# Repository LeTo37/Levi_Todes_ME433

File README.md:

# Levi_Todes_ME433
Advanced Mechatronics Homeworks

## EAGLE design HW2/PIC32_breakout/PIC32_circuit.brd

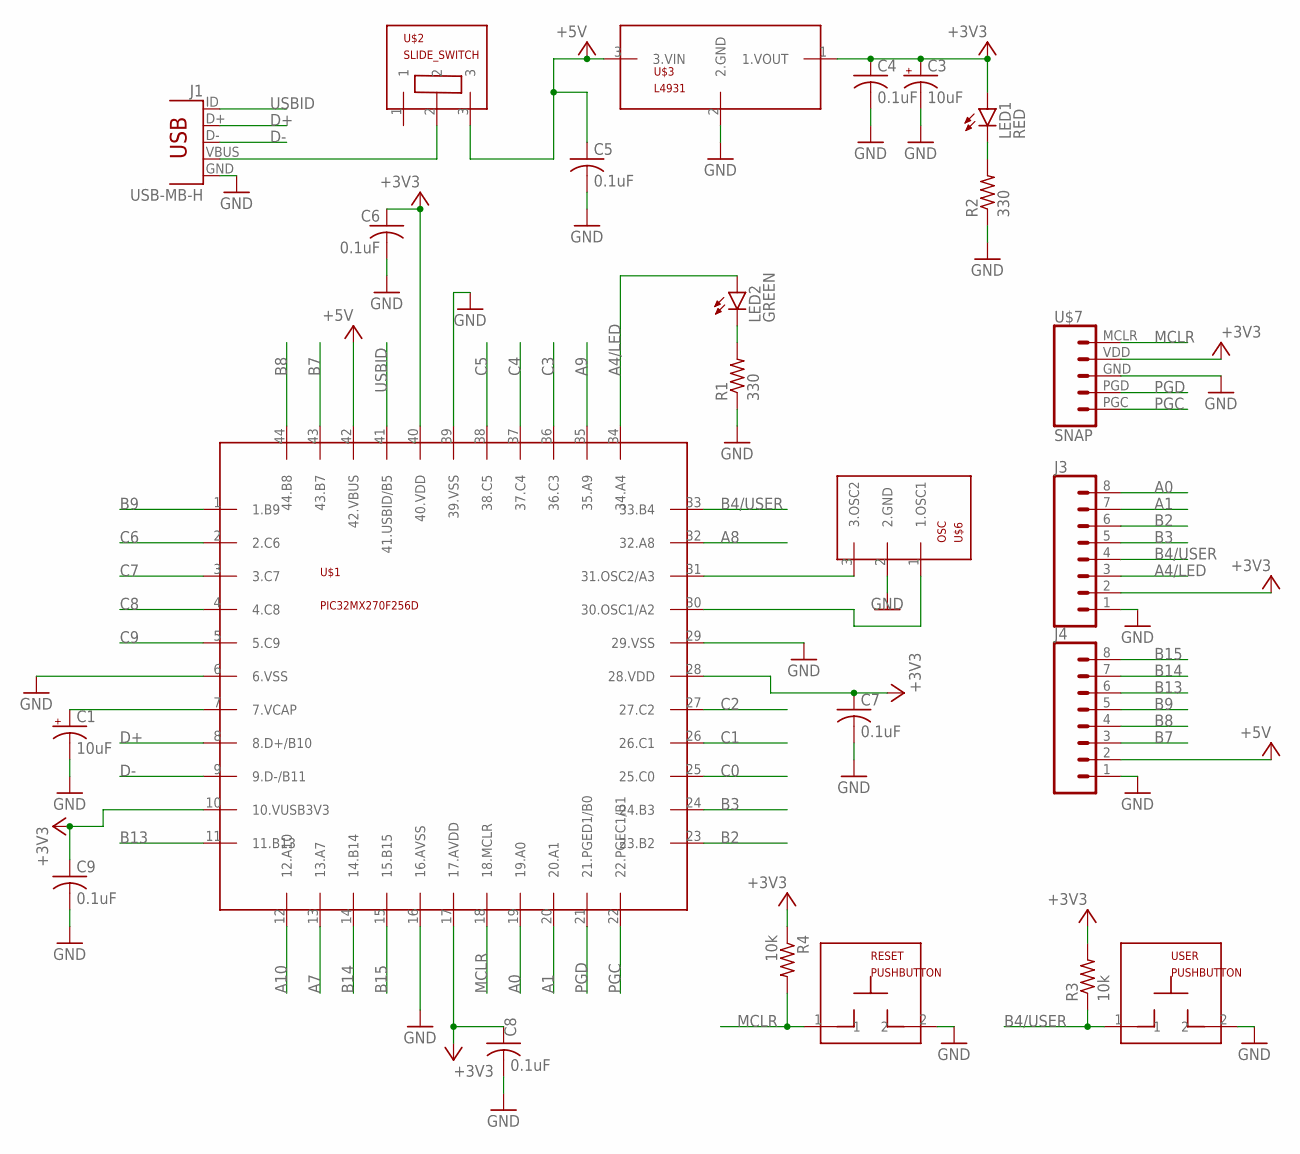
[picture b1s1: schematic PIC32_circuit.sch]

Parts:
C1, C3: 10uF; B45181B
C4, C5, C6, C7, C8, C9: 0.1uF; C025-025X050
J1: USB-MB-H
J3, J4: CONN_08"; 1X08
LED1: RED; LED3MM
LED2: GREEN; LED3MM
R1, R2: 330; 0207/10
R3, R4: 10k; 0207/10
RESET: PUSHBUTTON
U$1: PIC32MX270F256D; TQFP44
U$2: SLIDE_SWITCH
U$3: L4931; TO92-LINE
U$6: OSC
U$7: SNAP
USER: PUSHBUTTON

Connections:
+3V3: C3.+, C4.1, C6.1, C7.1, C8.1, C9.1, J3.2, LED1.A, R3.2, R4.1, U$1.10 (10.VUSB3V3), U$1.17 (17.AVDD), U$1.28 (28.VDD), U$1.40 (40.VDD), U$3.1 (1.VOUT), U$7.VDD
+5V: C5.1, J4.2, U$1.42 (42.VBUS), U$2.3, U$3.3 (3.VIN)
A0: J3.8, U$1.19 (19.A0)
A1: J3.7, U$1.20 (20.A1)
A4/LED: J3.3, LED2.A, U$1.34 (34.A4)
A7: U$1.13 (13.A7)
A8: U$1.32 (32.A8)
A9: U$1.35 (35.A9)
A10: U$1.12 (12.A10)
B2: J3.6, U$1.23 (23.B2)
B3: J3.5, U$1.24 (24.B3)
B4/USER: J3.4, R3.1, U$1.33 (33.B4), USER.1
B7: J4.3, U$1.43 (43.B7)
B8: J4.4, U$1.44 (44.B8)
B9: J4.5, U$1.1 (1.B9)
B13: J4.6, U$1.11 (11.B13)
B14: J4.7, U$1.14 (14.B14)
B15: J4.8, U$1.15 (15.B15)
C0: U$1.25 (25.C0)
C1: U$1.26 (26.C1)
C2: U$1.27 (27.C2)
C3: U$1.36 (36.C3)
C4: U$1.37 (37.C4)
C5: U$1.38 (38.C5)
C6: U$1.2 (2.C6)
C7: U$1.3 (3.C7)
C8: U$1.4 (4.C8)
C9: U$1.5 (5.C9)
D+: J1.D+, U$1.8 (8.D+/B10)
D-: J1.D-, U$1.9 (9.D-/B11)
GND: C1.-, C3.-, C4.2, C5.2, C6.2, C7.2, C8.2, C9.2, J1.GND, J3.1, J4.1, R1.1, R2.1, RESET.2, U$1.6 (6.VSS), U$1.16 (16.AVSS), U$1.29 (29.VSS), U$1.39 (39.VSS), U$3.2 (2.GND), U$6.2 (2.GND), U$7.GND, USER.2
MCLR: R4.2, RESET.1, U$1.18 (18.MCLR), U$7.MCLR
unnamed: U$1.31 (31.OSC2/A3), U$6.3 (3.OSC2)
unnamed: U$1.30 (30.OSC1/A2), U$6.1 (1.OSC1)
unnamed: LED1.K (C), R2.2
unnamed: LED2.K (C), R1.2
unnamed: J1.VBUS, U$2.2
unnamed: C1.+, U$1.7 (7.VCAP)
PGC: U$1.22 (22.PGEC1/B1), U$7.PGC
PGD: U$1.21 (21.PGED1/B0), U$7.PGD
USBID: J1.ID, U$1.41 (41.USBID/B5)

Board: 2 copper layers, 24 parts (0 on the bottom side), 27 nets, no tracks yet.

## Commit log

2019-04-03 Circuit built, images taken
2019-04-03 initial code
2019-04-04 final code
2019-04-16 HW4 - waves not perfect
2019-04-16 HW4 - triangle wave not perfect
2019-04-17 HW4 finished
2019-04-23 Homework 6-LCD
2019-05-01 HW7 - IMU -gyro bars
2019-05-01 circuit diagram hw5
2019-05-01 HW8 - IMU Gyros with Harmony
2019-05-04 HW9 - Touchscreen
2019-05-05 HW10 - CDC USB - IMU reader
2019-05-12 HW11 - DSP
2019-05-12 HW12 - mouse
2019-05-20 HW13 & HW14 - Mechanical Stuff
2019-05-20 readme
2019-05-20 smaller pics
2019-06-10 HW15 PWMs and LCD Plot
2019-06-14 final
2019-10-11 new vid
2019-10-11 added stls
2019-10-11 adding stls and pic
2019-10-11 stll update
